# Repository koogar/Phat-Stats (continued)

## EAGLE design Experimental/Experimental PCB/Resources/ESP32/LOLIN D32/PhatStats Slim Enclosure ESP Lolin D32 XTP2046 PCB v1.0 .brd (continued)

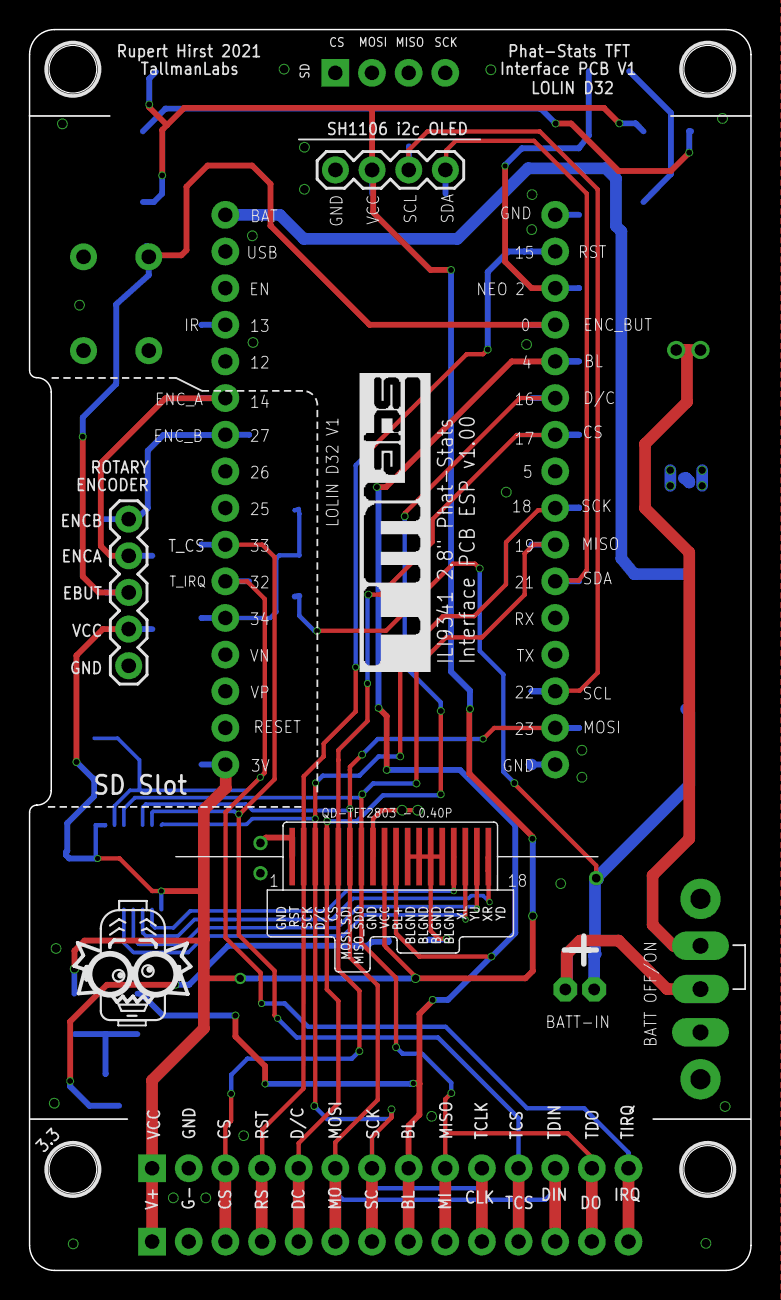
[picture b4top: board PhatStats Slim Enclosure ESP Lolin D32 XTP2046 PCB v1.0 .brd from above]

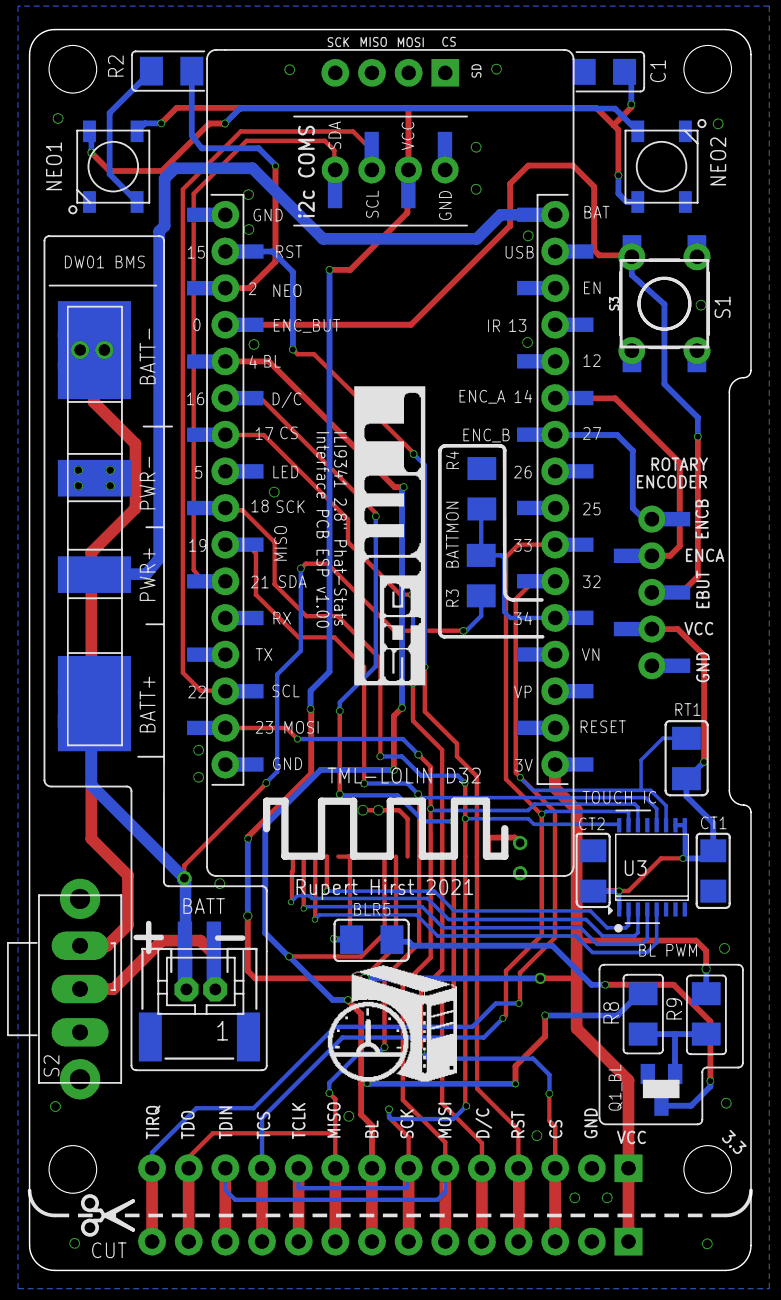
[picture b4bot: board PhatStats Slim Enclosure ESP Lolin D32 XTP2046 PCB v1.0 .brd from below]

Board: 2 copper layers, 50.0 x 86.0 mm, 35 parts (28 on the bottom side), 32 nets.

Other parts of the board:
U$6: MADPROF
U$8: HSMSMALL
U$9, U$10: TMSLOGO_INVERTED
U$13: SCISSORS_TS

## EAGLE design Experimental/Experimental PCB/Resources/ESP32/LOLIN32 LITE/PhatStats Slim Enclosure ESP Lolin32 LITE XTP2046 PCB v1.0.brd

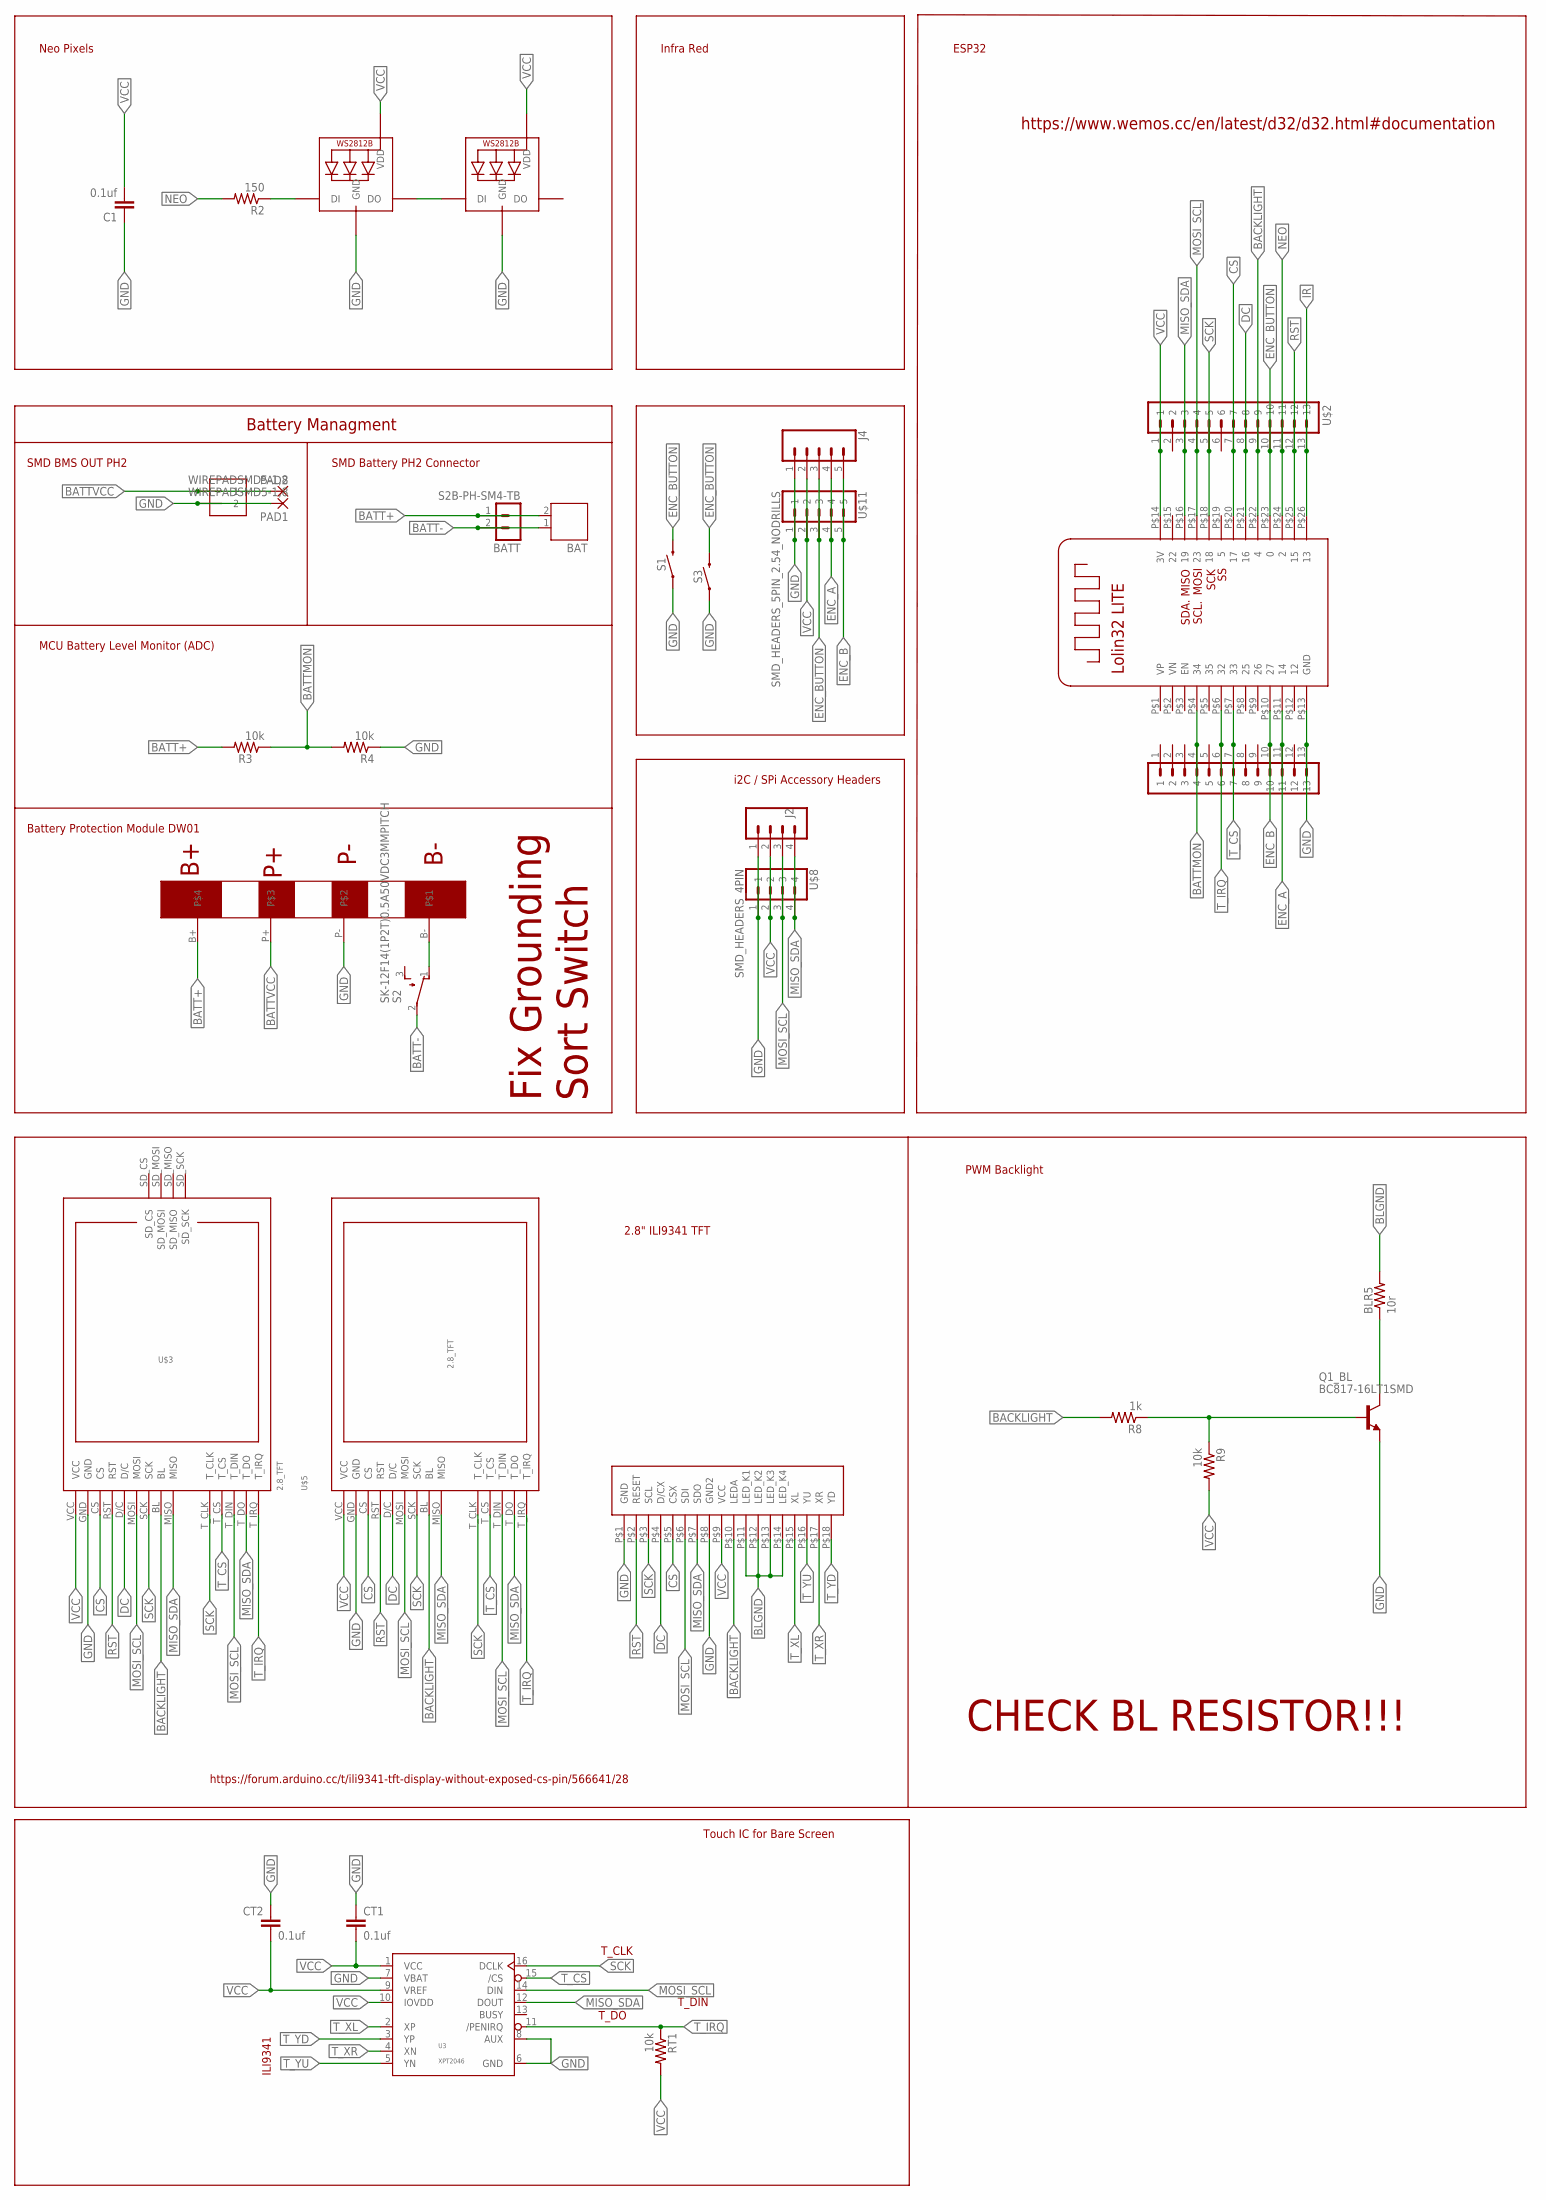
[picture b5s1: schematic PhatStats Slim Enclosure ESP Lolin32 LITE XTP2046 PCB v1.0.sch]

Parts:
0: ILI9341-2.8
BAT: JST-PH2
BATT: S2B-PH-SM4-TB
BLR5: 10r; M1206
C1: 0.1uf; C1206
CT1, CT2: 0.1uf; C1206
DW01-BMS: DW01BATTERYPROT
J1: 1X2-3.5MM
J2: CONN_04PTH; 1X04
J4: CONN_05; 1X05
NEO1, NEO2: WS2812B5050; WS2812B
PAD1, PAD2: WIREPADSMD5-1,8; 5-1,8
Q1_BL: BC817-16LT1SMD; SOT23-BEC
R2: 150; M1206
R3, R4, R9: 10k; M1206
R8: 1k; M1206
RT1: 10k; M1206
S1: MOMENTARY-SWITCH-SPST-PTH-6.0MM; TACTILE_SWITCH_PTH_6.0MM
S2: SK-12F14(1P2T)0.5A50VDC3MMPITCH
S3: MOMENTARY-SWITCH-SPST-SMD-6.2MM-TALL; TACTILE_SWITCH_SMD_6.2MM_TALL
U3: XPT2046; TSSOP-16
U$1, U$2: SMD_HEADERS_13PIN_2.54_NODRILLS; SMD_HEADERS_13PIN
U$3, U$5: 2.8_TFT
U$7: TML_LOLIND32_LITE
U$8: SMD_HEADERS_4PIN
U$11: SMD_HEADERS_5PIN_2.54_NODRILLS; SMD_HEADERS_5PIN

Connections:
BACKLIGHT: 0.P$10 (LEDA), R8.2, U$2.9, U$3.BL, U$5.BL, U$7.P$22 (4)
BATT+: BAT.2, BATT.1, DW01-BMS.B+, R3.2
BATT-: BAT.1, BATT.2, S2.2
BATTMON: R3.1, R4.2, U$1.4, U$7.P$4 (34)
BATTVCC: DW01-BMS.P+, J1.1, PAD2.1
BL: BLR5.1, Q1_BL.C
BLGND: 0.P$11 (LED_K1), 0.P$12 (LED_K2), 0.P$13 (LED_K3), 0.P$14 (LED_K4), BLR5.2
CS: 0.P$5 (CSX), U$2.7, U$3.CS, U$5.CS, U$7.P$20 (17)
DC: 0.P$4 (D/CX), U$2.8, U$3.D/C, U$5.D/C, U$7.P$21 (16)
ENC_A: J4.4, U$1.11, U$7.P$11 (14), U$11.4
ENC_B: J4.5, U$1.10, U$7.P$10 (27), U$11.5
ENC_BUTTON: J4.3, S1.3 (2), S3.B2 (2), U$2.10, U$7.P$23 (0), U$11.3
GND: 0.P$1 (GND), 0.P$8 (GND2), C1.1, CT1.1, CT2.1, DW01-BMS.P-, J1.2, J2.1, J4.1, NEO1.3-GND (GND), NEO2.3-GND (GND), PAD1.1, Q1_BL.E, R4.1, S1.1, S3.A2 (1), U3.6 (GND), U3.7 (VBAT), U3.8 (AUX), U$1.13, U$3.GND, U$5.GND, U$7.P$13 (GND), U$8.1, U$11.1
IR: U$2.13, U$7.P$26 (13)
MISO_SDA: 0.P$7 (SDO), J2.4, U3.12 (DOUT), U$2.3, U$3.MISO, U$3.T_DO, U$5.MISO, U$5.T_DO, U$7.P$16 (19), U$8.4
MOSI_SCL: 0.P$6 (SDI), J2.3, U3.14 (DIN), U$2.4, U$3.MOSI, U$3.T_DIN, U$5.MOSI, U$5.T_DIN, U$7.P$17 (23), U$8.3
unnamed: DW01-BMS.B-, S2.1 (O)
unnamed: NEO1.2-DOUT (DO), NEO2.4-DIN (DI)
unnamed: NEO1.4-DIN (DI), R2.1
unnamed: Q1_BL.B, R8.1, R9.1
NEO: R2.2, U$2.11, U$7.P$24 (2)
RST: 0.P$2 (RESET), U$2.12, U$3.RST, U$5.RST, U$7.P$25 (15)
SCK: 0.P$3 (SCL), U3.16 (DCLK), U$2.5, U$3.SCK, U$3.T_CLK, U$5.SCK, U$5.T_CLK, U$7.P$18 (18)
T_CS: U3.15 (/CS), U$1.7, U$3.T_CS, U$5.T_CS, U$7.P$7 (33)
T_IRQ: RT1.1, U3.11 (/PENIRQ), U$1.6, U$3.T_IRQ, U$5.T_IRQ, U$7.P$6 (32)
T_XL: 0.P$15 (XL), U3.2 (XP)
T_XR: 0.P$17 (XR), U3.4 (XN)
T_YD: 0.P$18 (YD), U3.3 (YP)
T_YU: 0.P$16 (YU), U3.5 (YN)
VCC: 0.P$9 (VCC), C1.2, CT1.2, CT2.2, J2.2, J4.2, NEO1.1-VDD (VDD), NEO2.1-VDD (VDD), R9.2, RT1.2, U3.1 (VCC), U3.9 (VREF), U3.10 (IOVDD), U$2.1, U$3.VCC, U$5.VCC, U$7.P$14 (3V), U$8.2, U$11.2

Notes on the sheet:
https://forum.arduino.cc/t/ili9341-tft-display-without-exposed-cs-pin/566641/28
SMD BMS OUT PH2
Battery Managment
SMD Battery PH2 Connector
MCU Battery Level Monitor (ADC)
Battery Protection Module DW01
Neo Pixels
Infra Red
i2C / SPi Accessory Headers
ESP32
2.8" ILI9341 TFT
PWM Backlight
CHECK BL RESISTOR!!!
https://www.wemos.cc/en/latest/d32/d32.html#documentation
Fix Grounding Sort Switch
ILI9341
T_CLK
T_DIN
T_DO
Touch IC for Bare Screen

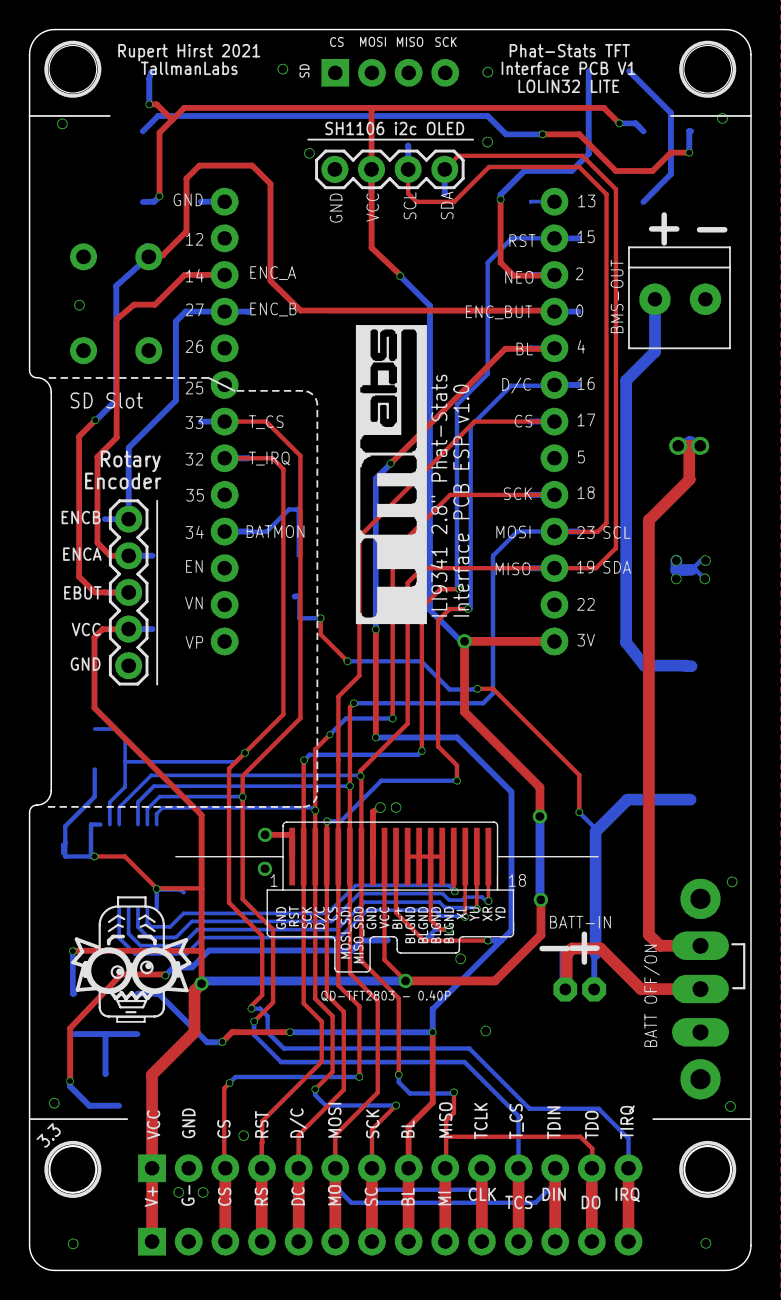
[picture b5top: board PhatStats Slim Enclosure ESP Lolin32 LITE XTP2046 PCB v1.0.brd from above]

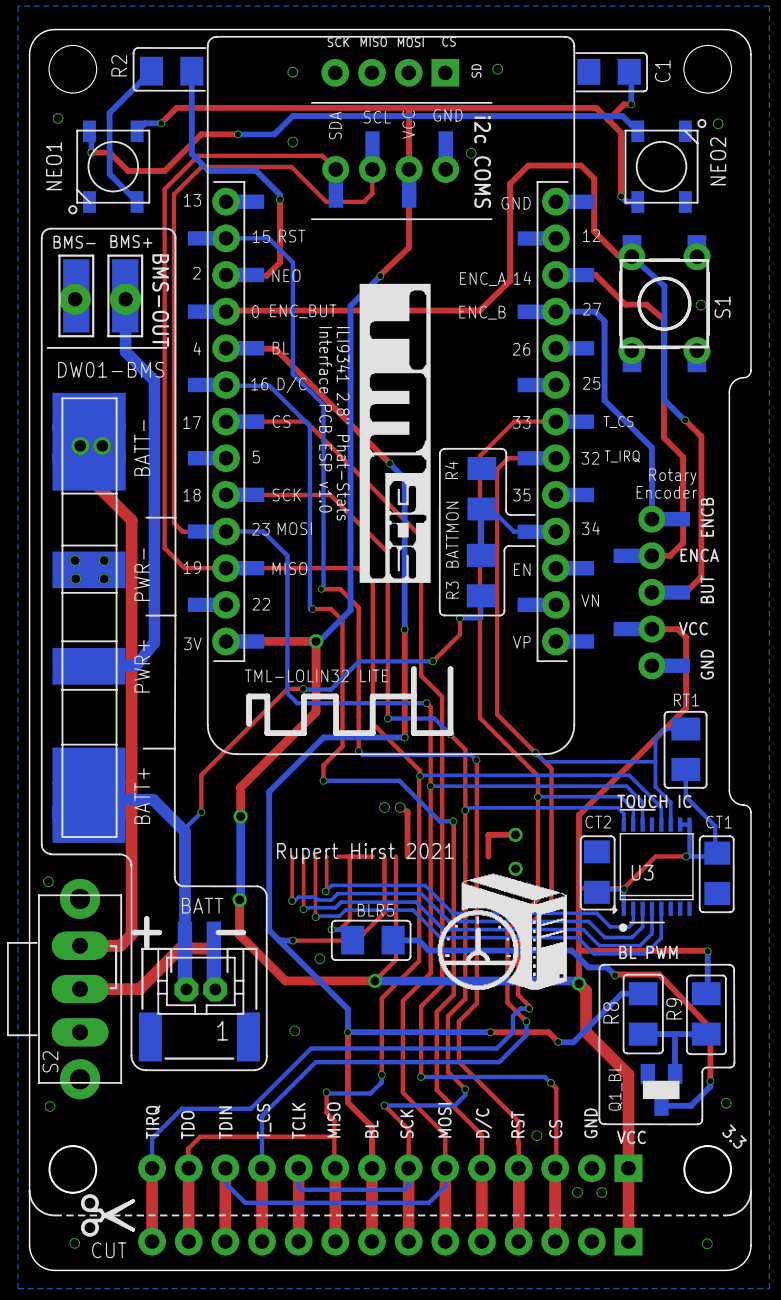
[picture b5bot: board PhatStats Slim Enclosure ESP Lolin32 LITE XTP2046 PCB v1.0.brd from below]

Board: 2 copper layers, 50.0 x 86.0 mm, 38 parts (30 on the bottom side), 30 nets.

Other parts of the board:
U$4: HSMSMALL
U$6: MADPROF
U$9, U$10: TMSLOGO_INVERTED
U$13: SCISSORS_TS

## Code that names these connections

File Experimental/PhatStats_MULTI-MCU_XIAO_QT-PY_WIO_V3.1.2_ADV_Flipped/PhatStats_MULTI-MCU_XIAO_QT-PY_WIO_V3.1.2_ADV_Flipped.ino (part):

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

/*
  eBay Special Red PCB pinouts VCC(3.3v), GND, CS, RST, D/C, MOSI, SCK, BL, (MISO, T_CLK, T_CS, T_DIN, T_DO, T_IRQ)

  ILI9341 SPI TFT Adafruit QT-PY / XIAO
  --------------------------------------
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
#define LCD_SPI SPI3
#define TFT_CS       LCD_SS_PIN
#define TFT_DC       LCD_DC
#define TFT_MOSI     LCD_MOSI_PIN
#define TFT_CLK      LCD_SCK_PIN
#define TFT_RST      LCD_RESET
#define TFT_MISO     LCD_MISO_PIN

Adafruit_ILI9341 tft = Adafruit_ILI9341(TFT_CS, TFT_DC, TFT_MOSI, TFT_CLK, TFT_RST, TFT_MISO);
#endif
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#if defined(Seeeduino_XIAO_RP2040) ^ defined(Seeeduino_XIAO_ESP32C3)
/* Mode Button pin*/
int mode_Button       = D1;
/* Screen TFT backlight Pin */
int TFT_backlight_PIN = D4;
#endif

#ifdef Seeeduino_WIO_ATSAMD51
/*Button pin*/
int mode_Button       = WIO_5S_PRESS; // (WIO JoyPad Button)
/* Screen TFT backlight Pin */
int TFT_backlight_PIN = LCD_BACKLIGHT;
#endif

#if defined(Seeeduino_XIAO_ATSAMD) ^ defined(Adafruit_QTPY_ATSAMD) ^ defined(Seeeduino_XIAO_NRF52840)
/* Mode Button pin*/
int mode_Button       = 1;
/* Screen TFT backlight Pin */
int TFT_backlight_PIN = 4;
#endif

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
  /* Set up PINs */
  pinMode(mode_Button, INPUT_PULLUP);
  pinMode(TFT_backlight_PIN, OUTPUT); // declare backlight pin to be an output:

  /* initializes the NeoPixel library */
  pixels.begin();
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#else

void backlightON () {
  analogWrite(TFT_backlight_PIN, brightness_count); // TFT turn on backlight
}
void backlightOFF () {
  analogWrite(TFT_backlight_PIN, 0);        // TFT turn off backlight,
}
#endif

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
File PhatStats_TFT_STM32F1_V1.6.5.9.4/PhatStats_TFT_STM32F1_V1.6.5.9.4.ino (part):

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  Bootloader:
  https://github.com/rogerclarkmelbourne/STM32duino-bootloader/tree/master/binaries

  BluePill_generic_boot20_pc13.bin  (On the "Bluepill" bootloader "_pc13" refers to the LED pin. )

  Important Upload Note:
  -----------------------
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#include "bitmap.h"

/*
  eBay Special Red PCB pinouots VCC(3.3v), GND, CS, RST, D/C, MOSI, SCK, BL, (MISO, T_CLK, T_CS, T_DIN, T_DO, T_IRQ)

  ILI9341 320x240 PINOUT
  --------------
  (TFT)
  CS     = PB11
  RST    = PB10
  DC     = PB1
  SCLK   = PA5
  MOSI   = PA7
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  /* ILI9321 TFT setup */
#include <Adafruit_ILI9341.h>  // v1.5.6 Adafruit Standard

/* STM32 SPi Hardware only for speed // STM32 SPi= CS:PB11 RST:PB10 DC:PB1 SCLK:PA5 MOSI:PA7*/
#define TFT_CS     PB11
#define TFT_DC     PB1
#define TFT_RST    PB10 // you can also connect this to the STM32 reset leave it undefined

/* These pins do not have to be defined as they are hardware pins */
//Connect TFT_SCLK to pin   PA5
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//---------------------------------------------------------------------------------------

/* Standard onboard LED for RX*/
#define RX_LEDPin PC13

/* Rotary Encoder*/
#define encoderOutA PB8 // CLK
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  pinMode (encoderOutA, INPUT);
  pinMode (encoderOutB, INPUT);
  pinMode(encoder_Button, INPUT_PULLUP);
  pinMode(TFT_backlight_PIN, OUTPUT); // declare backlight pin to be an output:
  pinMode(RX_LEDPin, OUTPUT); // STM32 BluePill Builtin LED /  HIGH(OFF) LOW (ON)
  backlightOFF();

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//-------------------------------------------  TFT Backlight  -------------------------------------------------------------

void backlightON () {
  analogWrite(TFT_backlight_PIN, TFT_brightness); // TFT turn on backlight
}

void backlightOFF () {

#ifdef Encoder_PWM_PNP
  analogWrite(TFT_backlight_PIN, 255);       // TFT turn off backlight  PWM 3906 Transitor 5v ,
#else
  analogWrite(TFT_backlight_PIN, 0);        // TFT turn off backlight fixed / no transistor 3.3v PWM ,
#endif

}
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
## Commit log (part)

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2021-10-04 add Lolin32 LITE & LolinD32
2023-02-26 clean up
2023-02-27 cleanup
2023-02-27 V3.0.0.KiSS [K]eep [i]t [S]toopid [S]imple
2023-03-01 Change Dir Name
2023-03-10 update images
2023-03-10 Add Multi MCU
2023-03-11 multiMCU
2023-03-13 Add More Boards
2023-03-13 update ESPC3
2023-03-13 add licence
2023-05-14 add seeed round tft
2025-05-11 Add Image for Hookup
